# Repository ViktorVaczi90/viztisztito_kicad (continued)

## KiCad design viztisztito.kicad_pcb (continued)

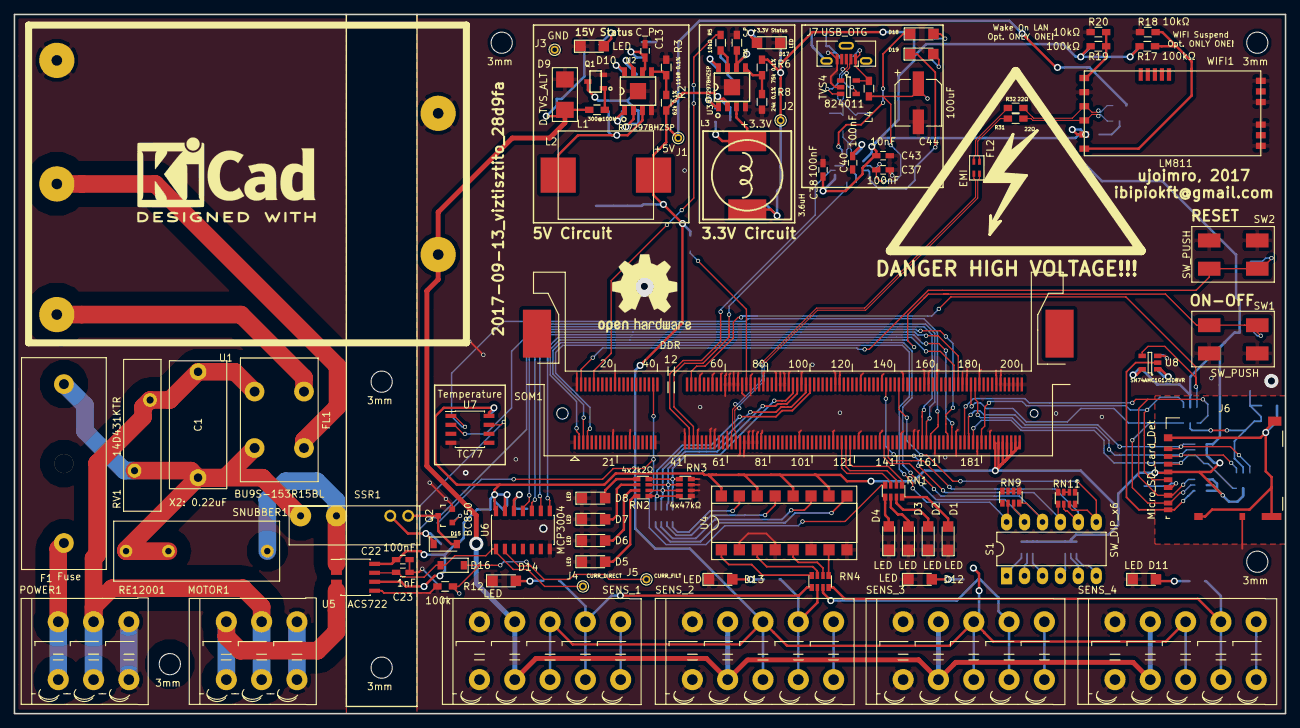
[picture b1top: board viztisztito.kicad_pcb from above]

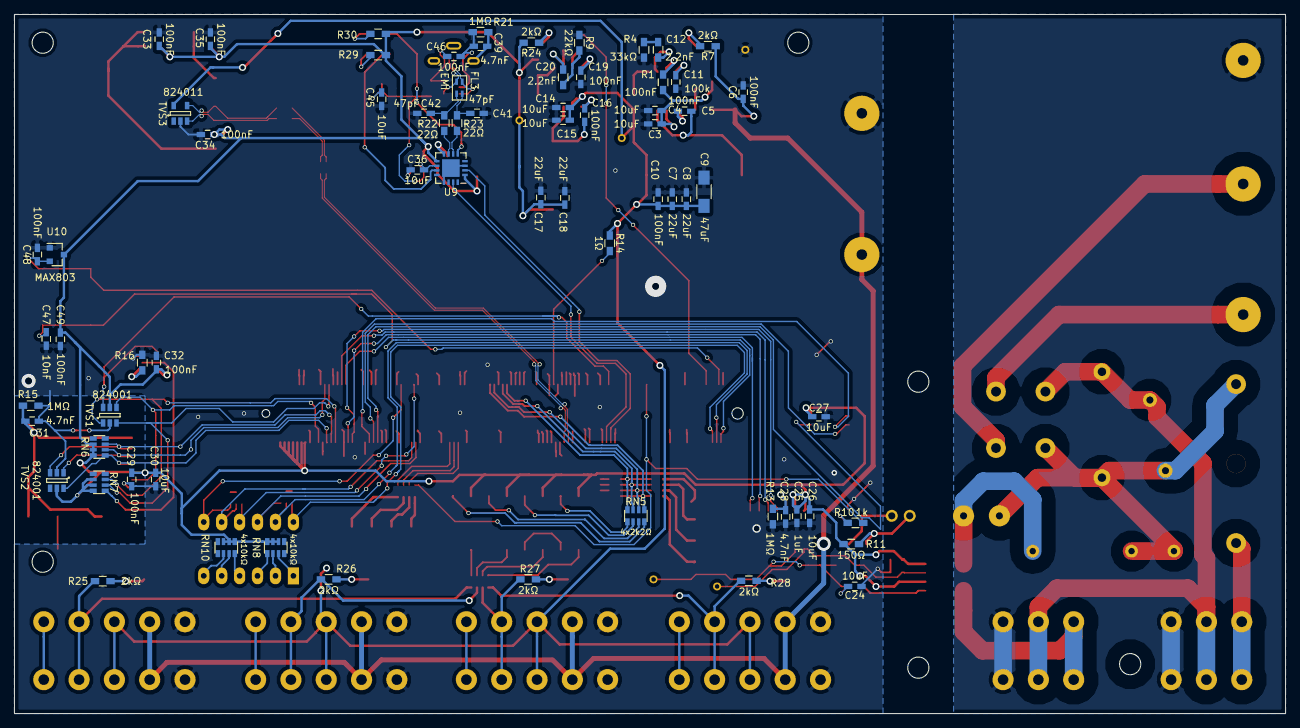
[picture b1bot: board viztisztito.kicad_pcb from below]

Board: 2 copper layers, 180.0 x 99.0 mm, 161 parts (69 on the bottom side), 125 nets.

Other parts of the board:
3mm, 3mm#2, 3mm#3, 3mm#4, 3mm#5, 3mm#6: Mounting Hole 3mm; Mounting_Hole_3mm

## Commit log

2015-10-20 sch almost ready
2015-10-20 sch ready, begining of layout
2015-10-20 layout beginning
2015-10-22 water level layout
2015-10-22 PWR layout
2015-10-22 almost ready
2015-10-23 only the main connector left
2015-10-23 little change in routes, not ready
2015-10-23 changes in GND routing
2015-10-27 maybe final
2015-10-28 some minor changes
2015-10-29 layout changes
2015-10-29 almost final...
2015-10-30 final?
2015-10-31 printed version
2016-01-18 save
2016-02-24 new layout, added psu
2016-02-24 small change in a cap
2016-02-25 change in a track
2016-02-26 added edge.cuts
2016-02-26 small trace change in power
2016-04-09 checked gerbers, possible problems in edge cuts?
2016-05-17 the version sent to Eurocircuits
2017-05-25 - this version has a new power supply 5V 15W - new water level sensing using protectbt
2017-05-25 water level simplification
2017-05-25 small changes
2017-05-25 fixes after consultation
2017-05-25 contact fix
2017-05-29 - snubber circuit added - diodes selected
2017-05-29 all components verified, pcb design required
2017-05-29 first version of the layout (not wired)
2017-05-30 backup before rewiring.
2017-05-30 this version has the parts organized; before routing
2017-05-30 all wired except forgotten and gnd and power
2017-05-30 this version has a complete pcb layout
2017-05-31 fixed links to the webpage of parts
2017-06-01 updated links
2017-06-09 stash commit before the revision of the parts
2017-06-10 parts corrected after review; dc/dc converter has to be ordered
2017-06-12 before wiring
2017-06-12 pcb wired
2017-06-12 shields corrected; wago connectors connected
2017-06-12 water level connectors
2017-06-12 auto verification
2017-06-13 before new pcb; - the order of the gpio pins have changed in accordance with olinuxino - indicator leds have been added for debugging - ad current pin added for debugging
2017-06-14 pcb configuration finished; the next task is the wiring
2017-06-14 pcb ready; missing: - correct the position of the text - debug information about the leds and the pins
2017-06-14 before final verification: - new wiring - control leds - control pins - clearance 10mm - annotations
2017-06-14 stash commit
2017-06-14 I have fixed the pcb of the 5 connectors
2017-06-14 I have added the notation of the water level sensors
2017-06-14 a minor change. The 3.3V pin was not properly annotated
2017-06-14 A few more moves + Credit Line
2017-06-15 I have fixed the pcb layouts of the parts based on verification of the physical part
2017-06-15 final commit before manufacturing
2017-06-15 power supply mirrored
2017-06-15 final changes:
    - fuse fix
    - annotation on the connectors water
    - annotation on the connectors power
2017-06-15 - eurocircuit fixes
2017-06-15 - npt holes - one D annotation corrected
2017-06-15 pwr annotation fixed
2017-06-15 brc checked
2017-06-18 printing the schematic
2017-06-18 a new, higher power dc/dc converter
2017-06-18 component
2017-06-25 Revert "brc checked"
    This reverts commit 47119418b3cd749e580adae0706d75db8872ec08.
2017-07-13 unconnect the 3.3V pin from olinuxino (it has an own dc-dc converter)
2017-08-23 this version generates the liteSOM pins without the LCD pins reasonably
2017-08-23 I have upgraded pwr module and ssr sensing module to accomodate the water level detectors.
2017-08-23 the schematic of the liteSOM module
2017-08-23 changes towards the liteSOM drive.
2017-08-23 liteSOM documentation
2017-08-28 this version contains all the important modules: - wifi - sd-card - usb-debug - litesom - gpio connections it does NOT contain the power module and the revision of the voltages
2017-08-28 Analog grounds and filtered reference voltage for the DAC.
2017-08-28 I have choosen a 20w 15v AC-DC converter, and have removed the rest of the converters. The power schema still has to be copied from the liteBoard.
2017-08-28 I have redirected the output of the acs722 current sensing module directly to the ad converter. In theory this should increase the scale of the current sensing.
2017-08-28 I have forgotten to add power to the usb converter chip
2017-08-28 minor change. I have connected the shield to the gnd.
2017-08-28 lib cache
2017-08-28 the water level is no longer isolated; I still use the optocouplers, but I have directly connected the ac/dc power line to the sensors.
2017-08-29 feature complete; the next step is the verification of the values and the schematics
2017-08-31 this version contains the datasheets and the footprints of the parts
2017-08-31 some issues fixed by the bugfixer; formal verification needed
2017-09-01 I have verified the schematic a second time (except the so-dimm), and I have selected all of the components with links and footprint. I need to verify the schematic a third time and root
2017-09-01 I have verified the so-dimm, and added 5V with an 1ohm resistor to drive the usb pins.
2017-09-01 part numbers generated;
    pcb generation started
2017-09-02 pcb. I have groupped the parts
2017-09-02 +5V and +3.3V positioned
2017-09-03 the text is now more visible
2017-09-03 the fuse is now protecting the ssr circle too, not just the ac-dc
2017-09-03 fuse protected ssr circle
2017-09-03 I have replaced the normal usb, with a vertical usb.
2017-09-03 the components roughly spaced on the pcb
2017-09-03 all the components placed I nead to beautify
2017-09-04 - the parts are moved to integer coordinates - the labels are moved, and now everything should be visible
2017-09-04 back parts moved to their places
2017-09-04 back label positions corrected
2017-09-04 back-front positions and labels verified
2017-09-04 correction in the serial-usb pinout
2017-09-04 new libst
2017-09-04 correction in the pinout of the usb-serial converter
2017-09-04 almost completely routed; few missing routes
2017-09-05 raw routing finished
2017-09-05 fully routed
2017-09-05 mounting holes and final touches
2017-09-05 BOM version
2017-09-06 This version contains the final revision before the part footprint verification.
    - The fuse is now moved outside of the power module before any parts
    - The wifi module has an additional pair of 22R differential resistors
    - The minor moves in the power power supply of the wifi module
2017-09-07 minor changes in the pcb
2017-09-07 bigger holes for the wire connectors and the ssr
2017-09-07 increased via and pad distances according to the eurocircuits specification
2017-09-07 I have replaced the 8xresistors to 4resistors because the distance between the pads was not big enough for the 3um copper layers
2017-09-07 wire distances
2017-09-07 wire distance
2017-09-07 wire differences
2017-09-07 remove backup files
2017-09-07 minor modifications
2017-09-10 minor changes:
    - I made Water Level Sensor label invisible
    - Few wires repositioned
2017-09-11 I have corrected the footprints of the parts which have arrived
2017-09-11 new disposition of the parts
2017-09-11 I have arranged the text, so all markup would be visible
2017-09-11 I have organized the text on the back side
2017-09-12 I have re-routed the table after the footprints of the parts have been verified.
2017-09-12 pcb re-routed, trying on eurocircuits
2017-09-12 I have fixed the errors from Eurocircuits.
2017-09-12 I had to regenerate the filled zones
2017-09-13 I have changed the isolation distance for the 30um copper.
2017-09-13 eurocircuit fixes
2017-09-13 gnd shield regeneration
2017-09-13 final changes before production
2017-09-13 production
2017-09-13 production export no real change
2017-09-13 ground connected on the bottom and the top plates
2017-09-13 label placement
